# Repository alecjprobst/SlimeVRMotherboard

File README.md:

# SlimeVR Motherboard

This is a project to make it easier to create SlimeVR trackers. This project reduces the amount of cable management needed when making SlimeVR trackers by providing a PCB that can be made for only $2. Beginner instructions on how to buy a PCB are below. Total cost should be around $55-60 for an enhanced core set excluding the cost of cases and straps.

# Sections

 - Parts and Setup
 - PCB Files and Submission
 - STL Files and Description
 - Assembly Instructions

## Parts and Setup

These PCB's use the official SlimeVR [Components](https://docs.slimevr.dev/diy/components-guide.html) and [Tracker Schematics](https://docs.slimevr.dev/diy/tracker-schematics.html). The PCB is compatible with either the BNO08X or MPU6050 IMU's and has locations for optional Battery Sense resistors and Charge Diodes. With this PCB, you will only need wire for connecting the IMU's. 

All of the parts below are linked in the SlimeVR [Components](https://docs.slimevr.dev/diy/components-guide.html) guide.
This PCB is made for use with the following parts:

 - D1 Mini
 - TP4056 Charging Board (any connector)
 - 3.7V Batteries
 - SS22F32 DPDT Switch
 - Either BNO08X or MPU6050 IMU's
 - (Optional) 180k ohm Battery Sense Resistor
 - (Optional) 1N5817 Charge Diodes

3D printable cases for the SlimeVR Trackers are included in this repo. They require no supports and no hardware to put together. See the STL Files and Description below

## PCB Files

All PCB files are included in this repo in the KiCAD Schematic Folder. Please feel free to modify them as you see fit. KiCAD was use to create this project which is a free and opensource tool to create PCB's. 

## PCB Submission 

Buying a PCB is very simple. Download this repo by clicking the green "Code" button towards the top of this page then click "Download ZIP". You will start downloading a ZIP file contain this entire repo. Open the zip file and find the "SlimeVR Motherboard Gerbers V1.2.rar" and "JLCPCB_Upload_Settings.png" file. Drag these to your desktop or a folder of your choice. 

To buy the PCB, we will use JLC PCB. Their website can be found here: https://jlcpcb.com/. Click on the text that says "Add gerber file" and find and select the "SlimeVR Motherboard Gerbers V1.2.rar" you just moved. Open the "JLCPCB_Upload_Settings.png" file and make sure the settings between the picture and what jlcpcb have shown you are the same. Feel free to change the PCB color to whatever you like (purple looks great!). Click "Save to Cart" then buy your PCB's. This process should be the same as any other online purchase from here on out.

## STL Files and Description

All STL's were created in Fusion360. Please feel free to modify them as you see fit. If you do not have a 3D printer, you can print the cases from jcpcb or you may want to consider 3D printing sites like [Hubs](https://www.hubs.com/3d-printing/) or [Sculpteo](https://www.sculpteo.com/en/).

Cases can be printed on an FDM printer at .2mm layer height.

A single SlimeVR Tracker case requires two parts, a Higher_Body.stl and a Lower_Body.stl. Both of these parts can be printed without supports. The Lower_Body.stl has poles to mount the PCB inside of the case so it does not shake. It is recommended to add hot glue to make sure the PCB does not move at all. Both cases have holes for charging and access to the D1 Mini as well as the switch and AUX tracker cable. The cases should slide together after being printed and should be somewhat difficult to pull apart.

## Assembly Instructions
A Knolled layout of all parts needed for one tracker is shown in this picture. Please note that your IMU's may look different and the resistor and diodes are optional.

To place the resistors, first bend them as shown below

Place these resistor and diodes as such

Solder the resistor and diodes as shown in the images below. Cut the excess wire when finished soldering.

To solder the TP4096, take 6 pins and place them as such

Solder them on both the top of the TP4096 and the bottom of the PCB as shown below. Cut the excess pins on the top and bottom when finished soldering.

To solder the D1 Mini, place two 1x8 pins in the holes as shown below.

Solder the top of the D1 Mini and bottom of the PCB as shown below. Cut the excess pins on the top and bottom when finished soldering.

Before soldering the switch, cut the excess hole mount as shown in the before and after pictures below.

To keep the Switch in place, it is recommended to use tape as shown below. Once secured, solder the switch from the bottom of the PCB. Cut the excess switch contacts after soldering

To add the IMU, first cut out 6 wires of around 25mm long and strip the ends of the wires as shown below.

Solder the wires as shown below. Generally it is easier to solder to the PCB first then the IMU but this may be personal preference. Cut the excess wire after soldering. Note: the AD0 wire is missing in the two pictures below and is required.

To Solder the AUX IMU, cut out 6 wires of either 150mm or 300mm in length. The 150mm is used for the ankle/foot IMU's while the 300mm is used for the chest/wait IMU's.

Solder the AUX IMU as shown below. Cut the excess wires after soldering.

To solder the battery, solder the ground (black) wire first then the power (red) wire second from the bottom of the PCB. Make sure these wires do not touch as it may cause sparks. Cut the excess wire when finished soldering.

It is recommended but not required to hot glue all parts as to prevent parts from moving inside the case. Hot gluing the wires will help protect from from strain as well. To assemble the case, put the battery in the Lower Body first.

Next, put the PCB on top of the battery with the ports facing the holes. The holes in the PCB should keep the PCB in place. Make sure that there are no excess wires or pins poking into the battery.

Hot glue the IMU to the Higher Body Case. Make sure the Higher Body Case is lined up correctly so the holes are facing the correct direction. 

Slide the Higher Body Case onto the Lower Body Case to close the SlimeVR Tracker. Make sure no wires get pinched or disconnected and the switch is able to be turned off and on. This completes the hardware assembly of the SlimeVR trackers. To setup the software, continue from the [SlimeVR Tracker Firmware Guide](https://docs.slimevr.dev/firmware/updating-firmware.html)

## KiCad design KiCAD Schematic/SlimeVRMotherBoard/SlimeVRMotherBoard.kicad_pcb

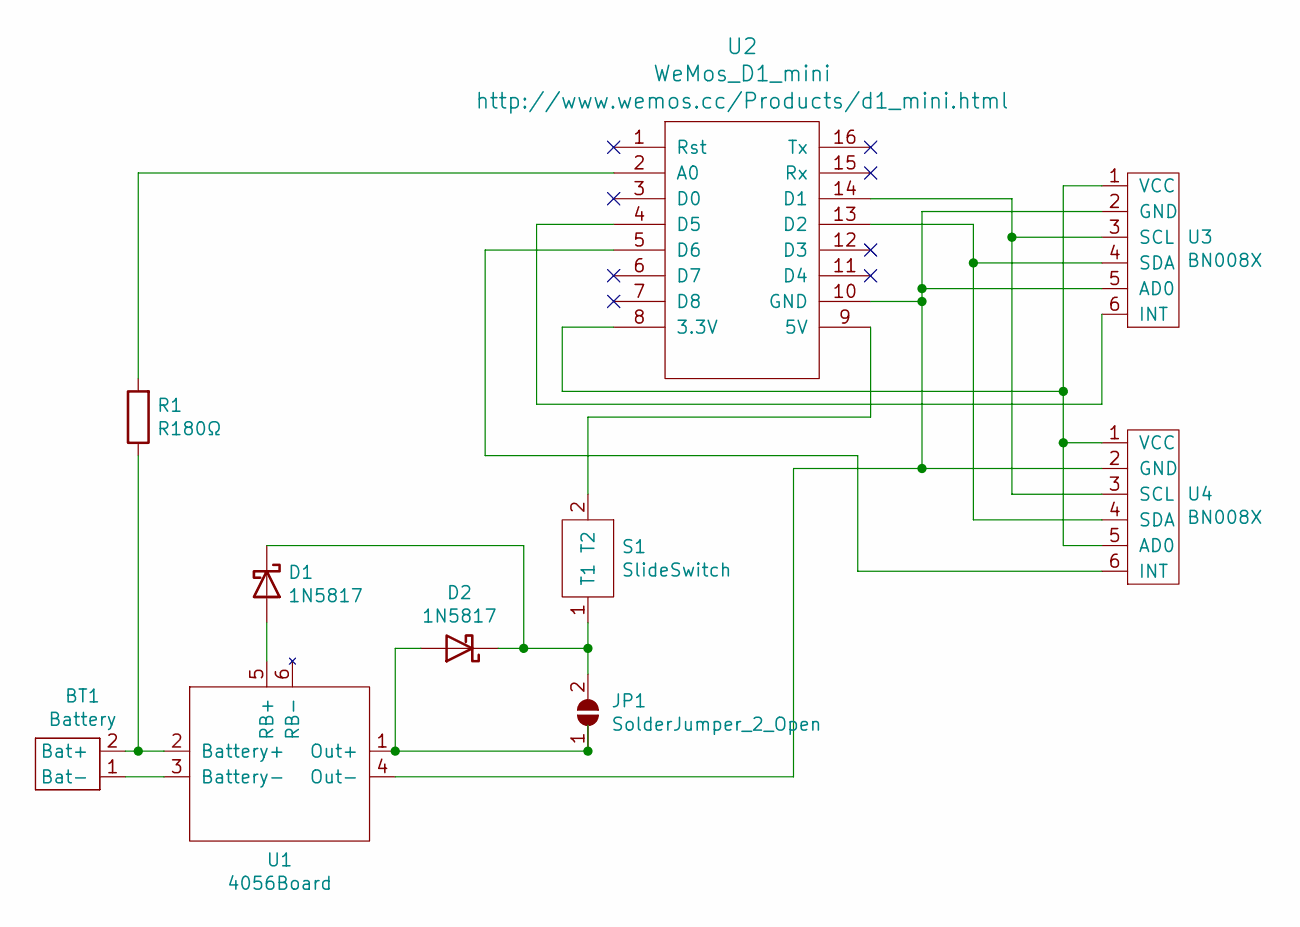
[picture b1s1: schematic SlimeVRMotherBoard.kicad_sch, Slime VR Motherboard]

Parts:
BT1: Battery
D1, D2: 1N5817; D_DO-41_SOD81_P10.16mm_Horizontal
JP1: SolderJumper_2_Open; SolderJumper-2_P1.3mm_Open_Pad1.0x1.5mm
R1: R180Ω; 180KΩ
S1: SlideSwitch; SS22F32
U1: 4056Board
U2: WeMos_D1_mini; wemos-d1-mini-connectors-only
U3, U4: BN008X; BNO080_Connector

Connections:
unnamed: BT1.1 (Bat-), U1.3 (Battery-)
unnamed: BT1.2 (Bat+), R1.1, U1.2 (Battery+)
unnamed: D1.1 (K), D2.1 (K), JP1.2 (B), S1.1 (T1)
unnamed: D1.2 (A), U1.5 (RB+)
unnamed: D2.2 (A), JP1.1 (A), U1.1 (Out+)
unnamed: R1.2, U2.2 (A0)
unnamed: S1.2 (T2), U2.9 (5V)
unnamed: U1.4 (Out-), U2.10 (GND), U3.2 (GND), U3.5 (AD0), U4.2 (GND)
unnamed: U2.4 (D5), U3.6 (INT)
unnamed: U2.5 (D6), U4.6 (INT)
unnamed: U2.8 (3.3V), U3.1 (VCC), U4.1 (VCC), U4.5 (AD0)
unnamed: U2.13 (D2), U3.4 (SDA), U4.4 (SDA)
unnamed: U2.14 (D1), U3.3 (SCL), U4.3 (SCL)

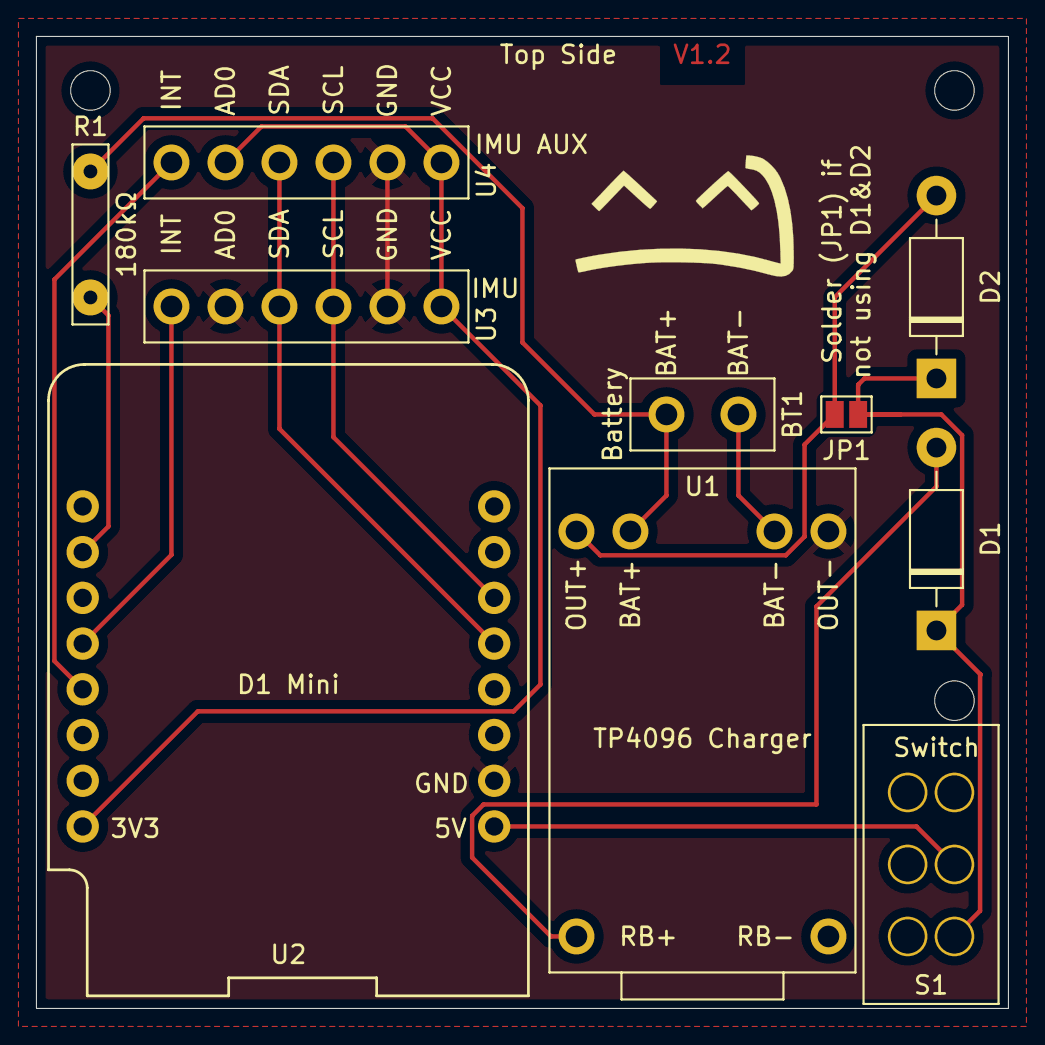
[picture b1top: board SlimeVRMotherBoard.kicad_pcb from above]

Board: 2 copper layers, 54.0 x 54.0 mm, 10 parts (0 on the bottom side), 13 nets.

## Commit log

2022-01-06 Initial Submission
2022-01-25 Updated board to V1.2 that fixed switch issue. Added new stl's for IMU cases
2022-02-04 Increase height of higher and lower body to fit trackers. Added pictures of build process
2022-02-05 Renamed Images so they are correctly labeled
2022-02-05 README Update Test
2022-02-05 Updated README.md with pictures
2022-02-05 Updated Pictures and README.md
2022-02-06 Fixed accidentally swapped Higher_Body and Higher_Body_IMU files
2022-03-08 Added LICENSE file to repo
2022-03-08 Fixed small text error in README specified file
2022-03-08 Changed License Type

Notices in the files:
KiCAD Schematic/SlimeVRMotherBoard/SlimeVRMotherBoard.kicad_pcb:
creativecommons.org/licenses/by/4.0
License: CC BY 4.0
